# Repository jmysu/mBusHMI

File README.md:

## mBusHMI

The mBusHMI Dev Board repository at GitHub <br>
This project is derived from mBusC3mini V2605, mainly change JST 1mm connectors to 2mm, add PICO 40p connector,<br>
change microUSB to TypeC, and add more features...<br>

---

---
[mBusC3mini V2605 Brief.pdf] (https://github.com/jmysu/mBusC3mini/blob/main/mBusC3mini%20V2605%20Brief.pdf)  <br>

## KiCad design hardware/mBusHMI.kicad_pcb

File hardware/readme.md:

mBusHMI hardware folder
---
Provide the PCB design files V2607(schematic/PCB layout) with KiCad10 format.<br>

As Autodesk stop the EAGLE PCB supporting and move to the cloud Fusion360, <br>
I choose the KiCad for faster PCB 3d renderning and circuit documentation. <br>

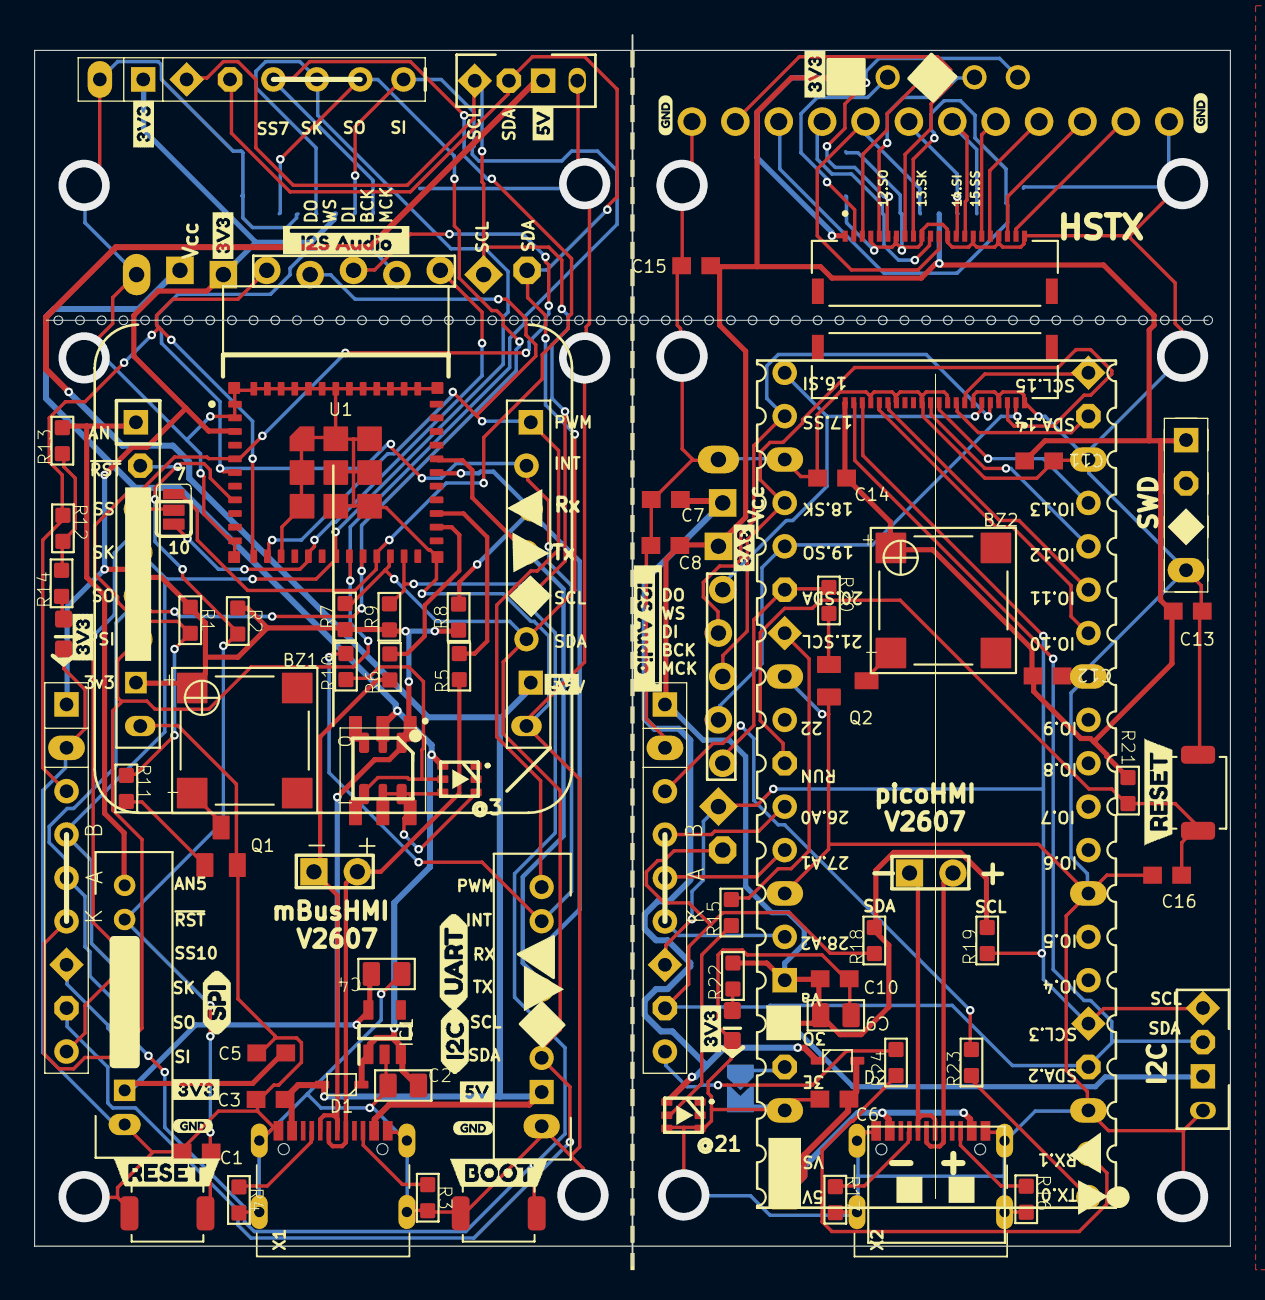
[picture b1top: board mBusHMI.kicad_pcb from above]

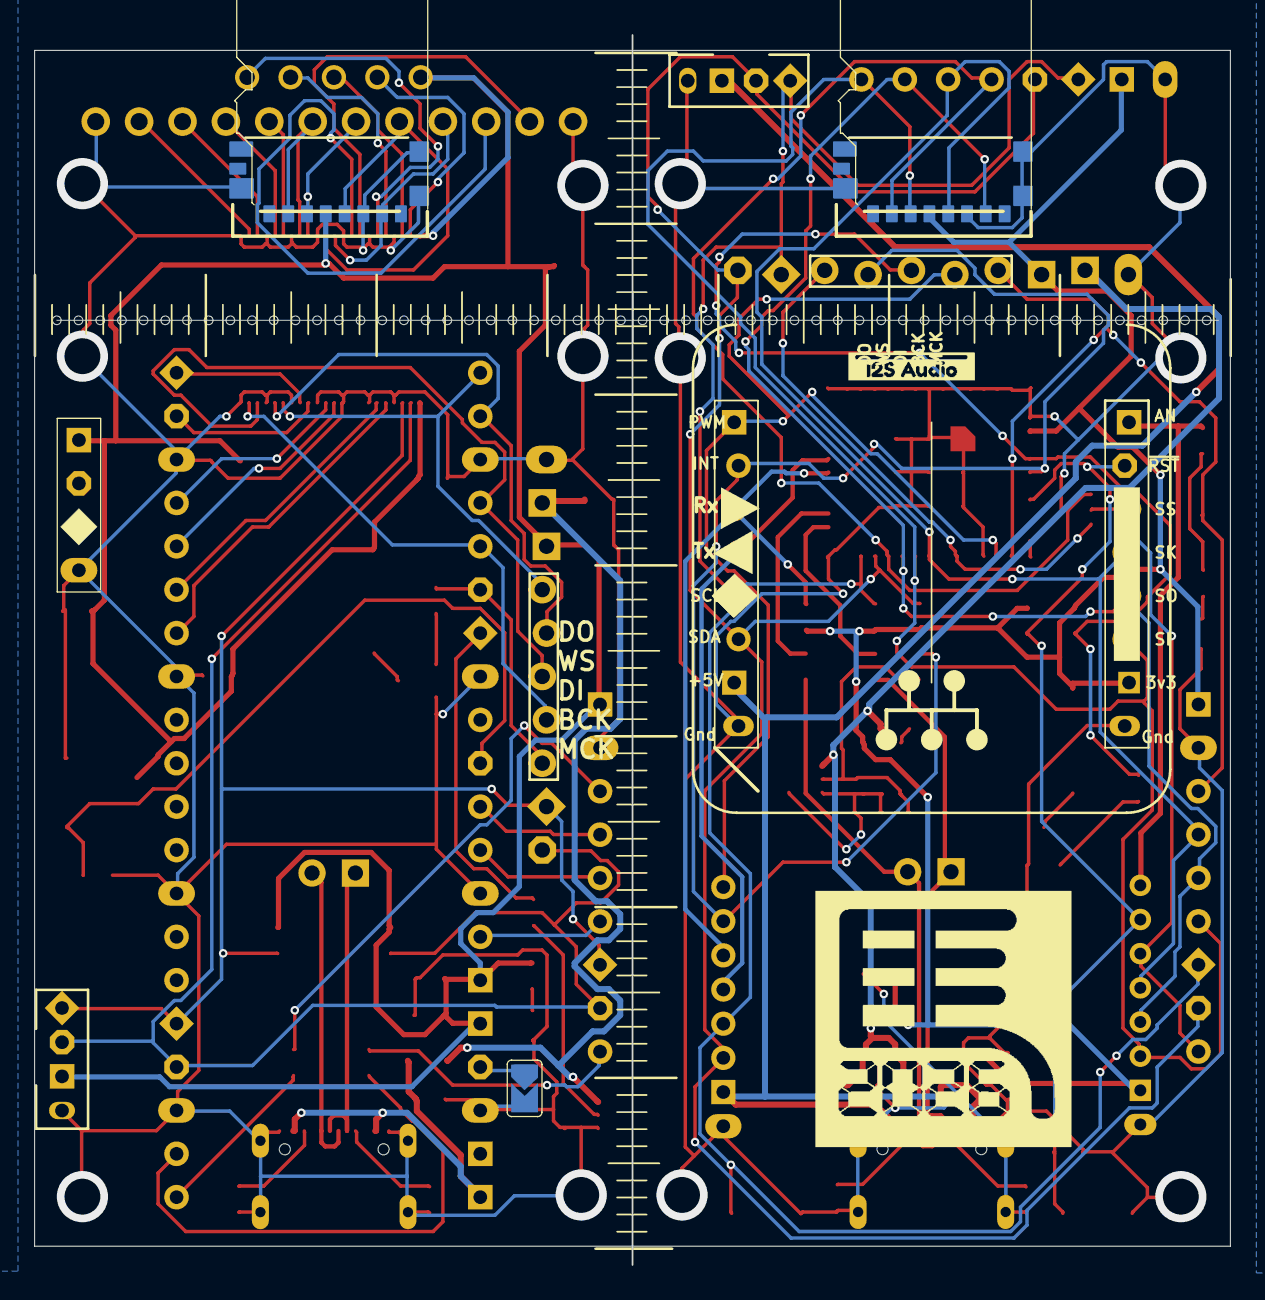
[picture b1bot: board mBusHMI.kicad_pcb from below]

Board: 2 copper layers, 70.0 x 72.0 mm, 160 parts (5 on the bottom side), 83 nets.

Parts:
$1_45_$_2026-06-27_02-17-04: LB_BOOT1
$1_47_$_2026-06-27_02-17-04: LB__I2S_AUDIO__
BZ1, BZ2: CMT-7525-80-SMT-TR; XDCR_CMT-7525-80-SMT-TR
C1, C3, C5, C6, C7, C8, C10, C13, C15, C16: 0.1uF; C0603
C2, C4, C9: 10uF; C0805
C11, C12, C14: 1uF; C0603
D1, D2: DIODE_PMEG3020EJ,115; SODFL2512X80N
IC1: AP7365-33WG-7; SOT95P285X130-5N
J1: JST_2MM_B8B-PH-K-SLEFT; B8B-PH-K-S-LEFT
J2: JST_2MM_B8B-PH-K-S; B8B-PH-K-S
J3, J9: DNP; 1X09_OLED_EC11
J4, J8: GROVE-CONNECTOR-DIPSCLSDA; GROVE_SCLSDA-2.0_NO
J5, J7: TF0475710001; MOLEX_0475710001
J6: HEADER-1X8-OLED-EC11; 1X08_OLED_EC11
J10, J11: FH55-22S-0.5SH; HRS_FH55-22S-0.5SH
JP1, JP4: PINHD-1X2NOSILK; 1X02_NOSILK
JP2: JUMPER-SMT_3_1-NC_PASTE_SILK; SMT-JUMPER_3_1-NC_PASTE_SILK
JP3, JP5: HEADER-1X10I2S; 1X10_ROUND_I2S_AUDIO
JP6: MICROBUILDER_HEADER-1X12; MICROBUILDER_1X12_ROUND
JP7: MICROBUILDER_HEADER-1X5ROUND; MICROBUILDER_1X05_ROUND
LB1: LB_UART
LB2: LB_5V
LB3, LB7, LB10, LB13, LB15, LB16, LB17: LB_3V; LB_3V3
LB4: LB_I2C
LB5: LB_SPI
LB6: LB_HORSE2026PNG
LB8: LB_RESET
LB9: LB_RESET; RESET0
LD1, LD2: GREEN; LED-0603
MB1: MIKROBUS_2X8
Q1, Q2: NMOS-BSS123; SOT23
R1, R2, R18, R19, R21, R22: 10K; R0603
R3, R4, R16, R17: 5.1K; R0603
R5, R6, R12, R23, R24: 33; R0603
R7, R8, R9: 4K7; R0603
R10, R11, R13, R15, R20: 330; R0603
R14: 660; R0603
RGB1, RGB3: WS2813-2020; WS2813C2020
RGB2: WS2813_3535; WS2813-50503535
RULER1, RULER2: RUTLER70MM; RULER70MM
SJ1: SOLDERJUMPER; SOLDERJUMPER_ARROW_NOPASTE
SW1, SW2, SW3: TACT4X3; SW_SPST_TS-1088-xR020
SWD1: SWD1X4; SWD_1X04
U1: ESP32-C3-MINI-1U-N4
U2: RPI_PICO_JGPIO; PICO-PKG-TH-GPIO
U$1, U$3, U$5, U$12: GND0
U$4, U$11: 5V0
U$6, U$8: #__I2S_AUDIO__0
UNK_HOLE_0: dummyfp0
UNK_HOLE_1: dummyfp1
UNK_HOLE_2: dummyfp2
UNK_HOLE_3: dummyfp3
UNK_HOLE_4: dummyfp4
UNK_HOLE_5: dummyfp5
UNK_HOLE_6: dummyfp6
UNK_HOLE_7: dummyfp7
UNK_HOLE_8: dummyfp8
UNK_HOLE_9: dummyfp9
UNK_HOLE_10: dummyfp10
UNK_HOLE_11: dummyfp11
UNK_HOLE_12: dummyfp12
UNK_HOLE_13: dummyfp13
UNK_HOLE_14: dummyfp14
UNK_HOLE_15: dummyfp15
UNK_HOLE_16: dummyfp16
UNK_HOLE_17: dummyfp17
UNK_HOLE_18: dummyfp18
UNK_HOLE_19: dummyfp19
UNK_HOLE_20: dummyfp20
UNK_HOLE_21: dummyfp21
UNK_HOLE_22: dummyfp22
UNK_HOLE_23: dummyfp23
UNK_HOLE_24: dummyfp24
UNK_HOLE_25: dummyfp25
UNK_HOLE_26: dummyfp26
UNK_HOLE_27: dummyfp27
UNK_HOLE_28: dummyfp28
UNK_HOLE_29: dummyfp29
UNK_HOLE_30: dummyfp30
UNK_HOLE_31: dummyfp31
UNK_HOLE_32: dummyfp32
UNK_HOLE_33: dummyfp33
UNK_HOLE_34: dummyfp34
UNK_HOLE_35: dummyfp35
UNK_HOLE_36: dummyfp36
UNK_HOLE_37: dummyfp37
UNK_HOLE_38: dummyfp38
UNK_HOLE_39: dummyfp39
UNK_HOLE_40: dummyfp40
UNK_HOLE_41: dummyfp41
UNK_HOLE_42: dummyfp42
UNK_HOLE_43: dummyfp43
UNK_HOLE_44: dummyfp44
UNK_HOLE_45: dummyfp45
UNK_HOLE_46: dummyfp46
UNK_HOLE_47: dummyfp47
UNK_HOLE_48: dummyfp48
UNK_HOLE_49: dummyfp49
UNK_HOLE_50: dummyfp50
UNK_HOLE_51: dummyfp51
UNK_HOLE_52: dummyfp52
UNK_HOLE_53: dummyfp53
X1, X2: USB-C; CUSB31-CFM2AX-01-X

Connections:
/4V3: C2.1, D1.1 (K), IC1.1 (IN), IC1.3 (EN), JP3.2, RGB1.6 (VDD), RGB2.2 (VDD), RGB2.8 (VDD)
/#4V3: C7.1, D2.1 (K), JP5.2, RGB3.6 (VDD)
/##RX: J9.1, R24.1
/##TX: J9.7, R23.1
/#GND: C6.2, C7.2, C8.2, C9.2, C10.2, C11.2, C12.2, C13.2, C14.2, C15.2, C16.2, J7.6 (VSS), J7.9 (GND@1), J7.10 (GND@2), J7.13 (GND@3), J8.4, J9.8, J10.4 (G_4), J10.7 (G_7), J10.10 (G_10), J10.13 (G_13), J10.16 (G_16), J10.19 (G_19), J10.22 (G_22), J11.1 (G_1), J11.4 (G_4), J11.7 (G_7), J11.10 (G_10), J11.13 (G_13), J11.16 (G_16), J11.19 (G_19), JP5.1, JP6.1, JP6.12, LD2.C, Q2.2 (S), R16.1, R17.1, RGB3.3 (GND), RGB3.4 (BI), SJ1.2, SWD1.1, U2.3 (GND), U2.8 (GND), U2.13 (GND), U2.18 (GND), U2.23 (GND), U2.28 (GND), U2.33 (GND), U2.38 (GND), X2.A1B12 (GND), X2.B1A12 (GND), X2.M1 (GND), X2.M2 (GND), X2.M3 (GND), X2.M4 (GND)
/#NEOPIX21: R15.1, U2.27 (GP21)
/#PICO_3V: BZ2.P, C8.1, C9.1, C10.1, C11.1, C12.1, C13.1, C14.1, C15.1, J7.4 (VDD), J8.3, J9.9, J10.1 (G_1), J11.22 (G_22), JP5.3, JP7.5, R18.1, R19.1, R21.2, R22.1, SWD1.4, U2.35 (ADC_REF), U2.36 (3V3(OUT))
/#RX: R24.2, U2.2 (GP1)
/#SCL: J8.1, J9.3, J11.20 (S_20), JP5.9, R19.2, U2.5 (GP3)
/#SDA: J8.2, J9.2, J11.21 (S_21), JP5.10, R18.2, U2.4 (GP2)
/#TX: R23.2, U2.1 (GP0)
/#USB5V: C6.1, D2.2 (A), U2.40 (VBUS), X2.A4B9 (VBUS), X2.B4A9 (VBUS)
/AD0_3V3: R12.1, R13.2, R14.1
/AN_5V: J1.8 (1), MB1.1 (AN), R13.1
/C3IO0: J3.7, JP3.4, R12.2, U1.12 (IO0)
/C3IO1: J2.1, JP3.5, MB1.16 (PWM), U1.13 (IO1)
/C3IO2: JP3.6, R1.1, R11.2, U1.5 (IO2)
/C3IO3: J2.2 (1), JP3.7, MB1.15 (INT), R10.1, U1.6 (IO3)
/C3IO4/SK: J1.5 (1), J3.6, J5.5 (CLK), J6.4 (3), MB1.4 (SCK), U1.18 (IO4)
/C3IO5/SI: J1.3 (1), J3.4, J5.3 (CMD), J6.2 (1), MB1.6 (MOSI), U1.19 (IO5)
/C3IO6/SO: J1.4 (1), J3.5, J5.7 (DAT0), J6.3 (2), MB1.5 (MISO), U1.20 (IO6)
/C3IO7/SS: J5.2 (DAT3/CD), J6.5 (4), JP2.1, U1.21 (IO7)
/C3IO8/SDA: J2.6 (1), J3.2, J4.2, J6.6 (5), JP3.10, MB1.11 (SDA), R7.1, U1.22 (IO8)
/C3IO10: JP2.3, JP3.8, U1.16 (IO10)
/C3IO18DD-: R6.2, U1.26 (IO18)
/C3IO19DD+: R5.2, U1.27 (IO19)
/C3RX: J2.3 (1), MB1.14 (RX), R8.1, U1.30 (RXD0)
/C3TX: J2.4 (1), MB1.13 (TX), U1.31 (TXD0)
/C3_3V: BZ1.P, C4.1, C5.1, IC1.5 (OUT), J1.2 (1), J3.9, J5.4 (VDD), J6.8 (7), JP3.3, MB1.7 (+3.3V), R1.2, R2.2, RGB2.1 (VCC), RGB2.7 (VCC), U1.3 (3V3)
/CAM_IO0: J10.6 (S_6), JP7.1
/CAM_IO1: J10.5 (S_5), JP7.2
/CAM_SCL: J10.3 (S_3), JP7.3
/CAM_SDA: J10.2 (S_2), JP7.4
/CC1: R4.2, X1.A5 (CC1)
/CC2: R3.2, X1.B5 (CC2)
/CCC1: R17.2, X2.A5 (CC1)
/CCC2: R16.2, X2.B5 (CC2)
/CK+: J7.3 (CMD), J10.14 (S_14), JP6.7
/CK-: J7.2 (DAT3/CD), J10.15 (S_15), JP6.6
/D0+: J10.20 (S_20), JP6.3
/D0-: J10.21 (S_21), JP6.2
/D1+: J10.17 (S_17), JP6.5
/D1-: J10.18 (S_18), JP6.4
/D2+: J7.7 (DAT0), J10.11 (S_11), JP6.9
/D2-: J7.5 (CLK), J10.12 (S_12), JP6.8
/D3+: J10.8 (S_8), JP6.11
/D3-: J10.9 (S_9), JP6.10
/D10: J11.18 (S_18), U2.14 (GP10)
/D11: J11.17 (S_17), U2.15 (GP11)
/D20: JP5.8, R20.2, U2.26 (GP20)
/D26/A0: J9.6, U2.31 (GP26)
/D27/A1: J9.5, U2.32 (GP27)
/D28/A2: J9.4, U2.34 (GP28)
/DD+: JP1.2, R5.1, X1.A6 (D+), X1.B6 (D+)
/DD-: JP1.1, R6.1, X1.A7 (D-), X1.B7 (D-)
/DI: R10.2, RGB1.5 (DI_2), RGB2.4 (DIN), RGB2.10 (DIN)
/DO: RGB2.3 (DO), RGB2.9 (DO)
/GND: C1.2, C2.2, C3.2, C4.2, C5.2, IC1.2 (GND), J1.1, J2.8 (1), J3.8, J4.4, J5.6 (VSS), J5.9 (GND@1), J5.10 (GND@2), J5.13 (GND@3), J6.9 (8), JP3.1, LD1.C, MB1.8 (GND@1), MB1.9 (GND@2), Q1.2 (S), R3.1, R4.1, U1.1 (GND), U1.2 (GND), U1.11 (GND), U1.14 (GND), U1.36 (GND), U1.37 (GND), U1.38 (GND), U1.39 (GND), U1.40 (GND), U1.41 (GND), U1.42 (GND), U1.43 (GND), U1.44 (GND), U1.45 (GND), U1.46 (GND), U1.47 (GND), U1.48 (GND), U1.49_1 (GND), U1.49_2 (GND), U1.49_3 (GND), U1.49_4 (GND), U1.49_5 (GND), U1.49_6 (GND), U1.49_7 (GND), U1.49_8 (GND), U1.49_9 (GND), U1.50 (GND), U1.51 (GND), U1.52 (GND), U1.53 (GND), X1.A1B12 (GND), X1.B1A12 (GND), X1.M1 (GND), X1.M2 (GND), X1.M3 (GND), X1.M4 (GND)
/HSTX12.D2+: J11.12 (S_12), U2.16 (GP12)
/HSTX13.D2-: J11.11 (S_11), U2.17 (GP13)
/HSTX14.CK+: J11.9 (S_9), U2.19 (GP14)
/HSTX15.CK-: J11.8 (S_8), U2.20 (GP15)
/HSTX16.D1+: J11.6 (S_6), JP5.4, U2.21 (GP16)
/HSTX17.D1-: J11.5 (S_5), JP5.5, U2.22 (GP17)
/HSTX18.D0+: J11.3 (S_3), JP5.6, U2.24 (GP18)
/HSTX19.D0-: J11.2 (S_2), JP5.7, U2.25 (GP19)
/LED: LD1.A, R14.2
/NEO_DI: R15.2, RGB3.5 (DI_2)
/SCL/~C3BOOT: J2.5 (1), J3.3, J4.1, J6.7 (6), JP3.9, MB1.12 (SCL), R9.1, U1.23 (IO9)
/USB5V: C3.1, D1.2 (A), J2.7 (1), J4.3, MB1.10 (+5V), X1.A4B9 (VBUS), X1.B4A9 (VBUS)
/USBD+: JP4.2, X2.A6 (D+), X2.B6 (D+)
/USBD-: JP4.1, X2.A7 (D-), X2.B7 (D-)
/~$C3CS10: J1.6 (1), J3.1, JP2.2, MB1.3 (CS)
/~$C3RST: C1.1, J1.7 (1), MB1.2 (RST), R2.1, U1.8 (EN)
/~RESET: C16.1, R21.1, U2.30 (RUN)
unnamed: LD2.A, R22.2
unnamed: BZ1.N, Q1.3 (D)
unnamed: Q1.1 (G), R11.1
unnamed: BZ2.N, Q2.3 (D)
unnamed: Q2.1 (G), R20.1
unnamed: R7.2, R8.2, R9.2
unnamed: RGB1.3 (GND), RGB1.4 (BI), RGB2.5 (GND), RGB2.6 (BIN), RGB2.11 (GND), RGB2.12 (BIN)
unnamed: SJ1.1, U2.37 (3V3_EN)

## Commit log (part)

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2026-06-28 Add bottom image to README
    Updated README to include bottom image of the mBusHMI Dev Board.
2026-06-28 Update image in README.md
    Replaced mBusHM image with mBusHMI image in README.
2026-06-28 Add HTML line breaks in README content
    Updated README to include HTML line breaks.
2026-06-28 Update README to mention additional features
    Added a note about additional features to the README.
2026-06-28 Revise README.md project description
    Updated project description for clarity and accuracy.
2026-06-28 Fix formatting and update project description in README
2026-06-28 Revise README.md for clarity and formatting
    Updated project description and fixed formatting issues.
2026-06-28 Correct title formatting in README.md
    Fixed formatting of the project title in README.
2026-06-28 Update KiCad format version in README
2026-06-28 Correct image tag in hardware README
    Fix HTML entity encoding for image tag in README.
2026-06-28 Fix image paths in hardware readme
    Updated image source paths in the readme.
2026-06-29 Revise KiCad justification for PCB design choice
    Updated the description to emphasize faster PCB rendering.
